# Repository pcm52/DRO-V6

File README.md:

# DRO-V6
Digital Readout sketch files for the Arduino IDE

Schematic and PCB layout files for both the DRO and Encoder boards in Eagle format.

See pcm52.com for more details on construction.

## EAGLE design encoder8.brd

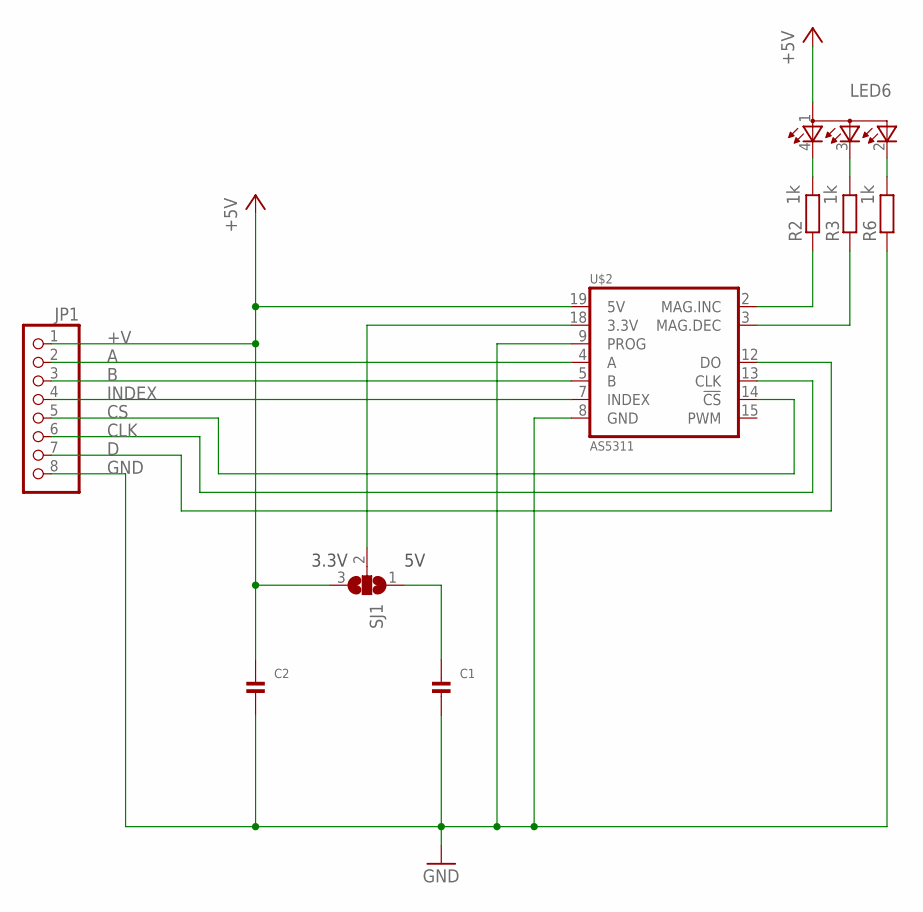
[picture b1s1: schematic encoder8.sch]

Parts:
C1, C2: CAP_CERAMIC0805; 0805
JP1: PINHD-1X8BIG; 1X08-BIG
LED6: RGB; RGB_LED_0805
R2, R3, R6: 1k; M0805
SJ1: SJ2W; SJ_2
U$2: AS5311; TSSOP.20

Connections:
+5V: LED6.1 (CA)
+V: C2.1, JP1.1, SJ1.3, U$2.19 (5V)
A: JP1.2, U$2.4 (A)
B: JP1.3, U$2.5 (B)
CLK: JP1.6, U$2.13 (CLK)
CS: JP1.5, U$2.14 (!CS)
D: JP1.7, U$2.12 (DO)
DEC: R3.1, U$2.3 (MAG.DEC)
GND: C1.2, C2.2, JP1.8, R6.1, U$2.8 (GND), U$2.9 (PROG)
INC: R2.1, U$2.2 (MAG.INC)
INDEX: JP1.4, U$2.7 (INDEX)
unnamed: C1.1, SJ1.1
unnamed: LED6.4 (CRED), R2.2
unnamed: LED6.3 (CGREEN), R3.2
unnamed: LED6.2 (CBLUE), R6.2
unnamed: SJ1.2, U$2.18 (3.3V)

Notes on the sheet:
3.3V

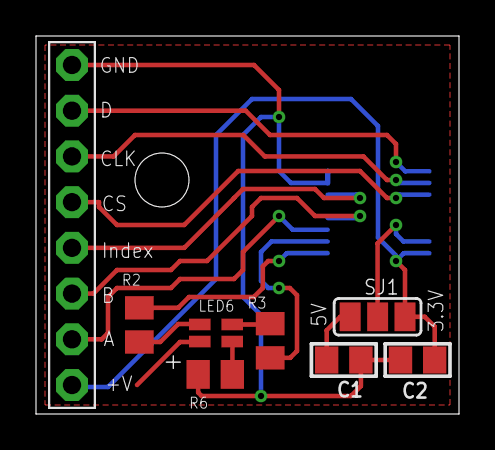
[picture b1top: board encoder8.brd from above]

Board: 2 copper layers, 23.5 x 21.0 mm, 9 parts (1 on the bottom side), 15 nets.

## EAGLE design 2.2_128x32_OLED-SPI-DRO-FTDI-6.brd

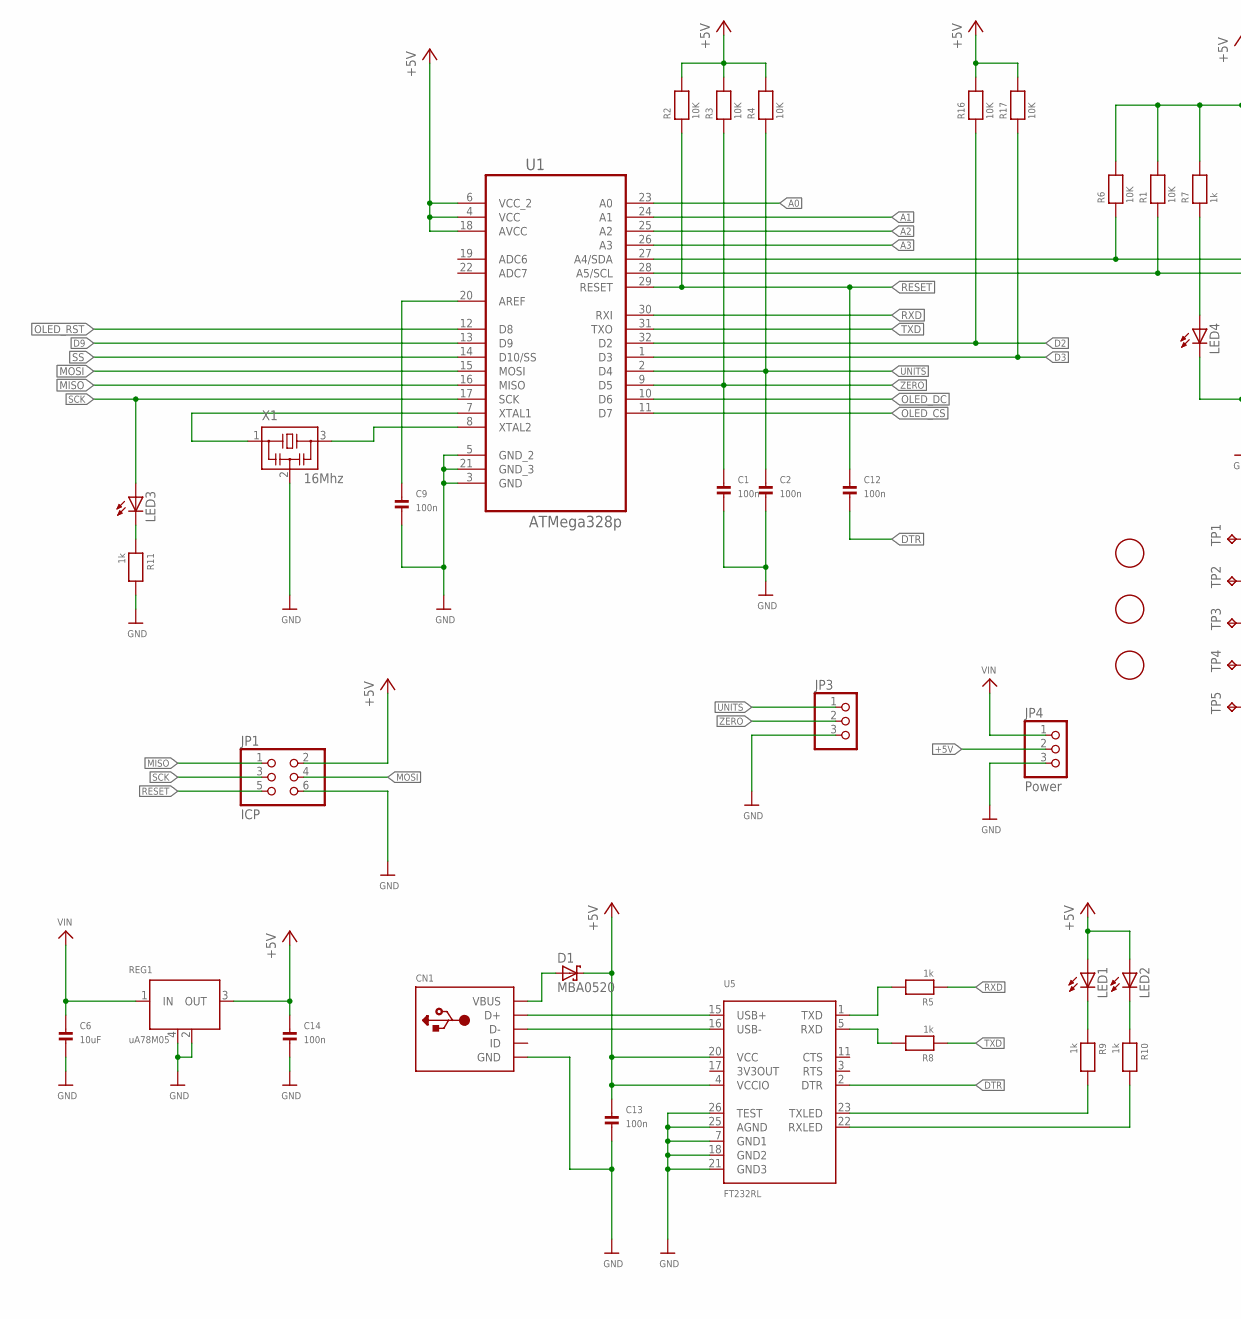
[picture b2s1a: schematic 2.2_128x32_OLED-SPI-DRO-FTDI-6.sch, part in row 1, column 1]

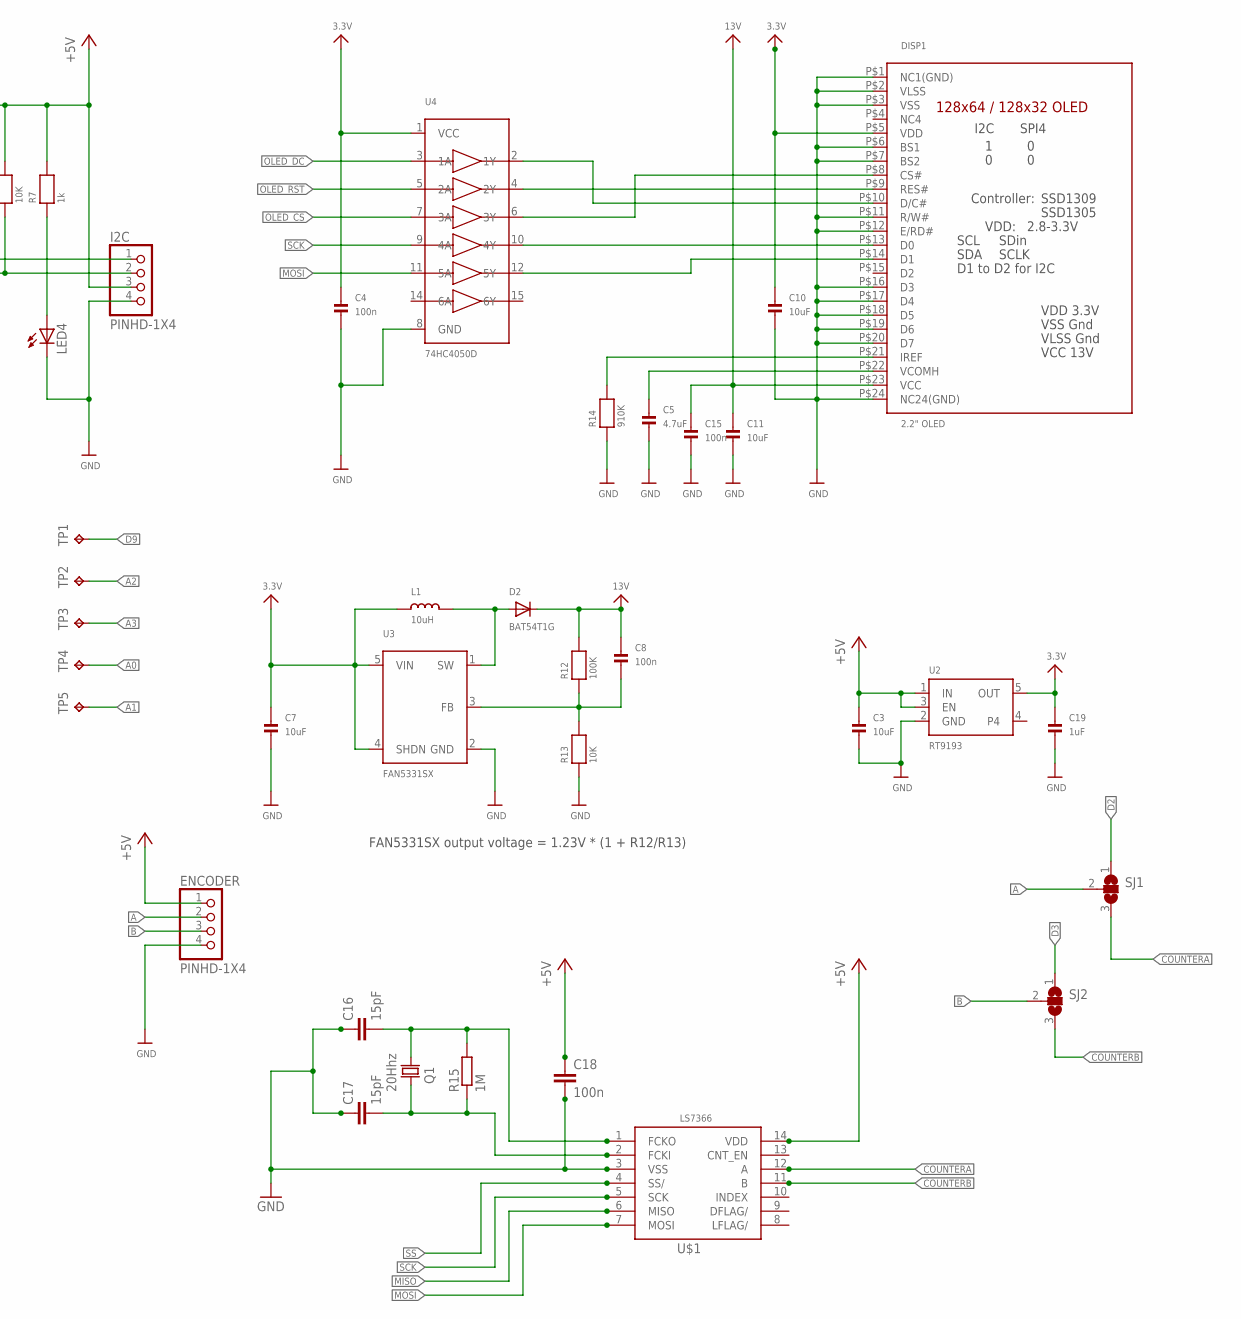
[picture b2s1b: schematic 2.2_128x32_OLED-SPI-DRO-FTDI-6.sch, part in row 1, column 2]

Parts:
C1, C2, C4, C8, C9, C12, C13, C14, C15: 100n; 0805
C3, C6, C7, C10, C11: 10uF; 0805
C5: 4.7uF; 0805
C16, C17: 15pF; C0805
C18: 100n; C0805
C19: 1uF; 0805
CN1: USBMINIB; USB-MINIB
D1: MBA0520; SOD123
D2: BAT54T1G; SOD-123
DISP1: 2.2" OLED; 1.5-128X64-TOP-CONTACT
ENCODER: PINHD-1X4; 1X04-BIG
I2C: PINHD-1X4; 1X04-BIG
JP1: ICP; 2X03
JP3: PINHD-1X3; 1X03
JP4: Power; 1X03
L1: 10uH; INDUCTOR_1007
LED1, LED2, LED3, LED4: LEDCHIPLED_0805; CHIPLED_0805
Q1: 20Hhz; F6-XTAL
R1, R2, R3, R4, R6, R13, R16, R17: 10K; 0805
R5, R7, R8, R9, R10, R11: 1k; 0805
R12: 100K; 0805
R14: 910K; 0805
R15: 1M; M0805
REG1: uA78M05; UA78M05
SJ1, SJ2: SJ2W; SJ_2
TP1, TP2, TP3, TP4, TP5: TPTP08R; TP08R
U1: ATMega328p; TQFP-32
U2: RT9193; SOT23-5
U3: FAN5331SX; SOT23-5
U4: 74HC4050D; SOIC16
U5: FT232RL; SSOP28DB
U$1: LS7366; SO14
U$2, U$6, U$28: FIDUCIAL; FIDUCIAL_1MM
X1: 16Mhz; CSTCE-CRYSTAL-OSC

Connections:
3.3V: C4.1, C7.1, C10.1, C19.1, DISP1.P$5 (VDD), L1.P$1 (1), U2.5 (OUT), U3.4 (SHDN), U3.5 (VIN), U4.1 (VCC)
3V3OUT: U5.17 (3V3OUT)
13V: C8.1, C11.1, C15.1, D2.C, DISP1.P$23 (VCC), R12.2
+5V: C3.1, C13.1, C14.1, C18.1, D1.C, ENCODER.1, I2C.3, JP1.2, JP4.2, LED1.A, LED2.A, R1.2, R2.2, R3.2, R4.2, R6.2, R7.2, R16.2, R17.2, REG1.3 (OUT), U1.4 (VCC), U1.6 (VCC_2), U1.18 (AVCC), U2.1 (IN), U2.3 (EN), U5.4 (VCCIO), U5.20 (VCC), U$1.14 (VDD)
A: ENCODER.2, SJ1.2
A0: TP4.TP, U1.23 (A0)
A1: TP5.TP, U1.24 (A1)
A2: TP2.TP, U1.25 (A2)
A3: TP3.TP, U1.26 (A3)
B: ENCODER.3, SJ2.2
COUNTERA: SJ1.3, U$1.12 (A)
COUNTERB: SJ2.3, U$1.11 (B)
CS: DISP1.P$8 (CS#), U4.6 (3Y)
D0: DISP1.P$13 (D0), U4.10 (4Y)
D1: DISP1.P$14 (D1), U4.12 (5Y)
D2: R16.1, SJ1.1, U1.32 (D2)
D3: R17.1, SJ2.1, U1.1 (D3)
D9: TP1.TP, U1.13 (D9)
DC: DISP1.P$10 (D/C#), U4.2 (1Y)
DTR: C12.2, U5.2 (DTR)
GND: C1.2, C2.2, C3.2, C4.2, C5.2, C6.2, C7.2, C9.2, C10.2, C11.2, C13.2, C14.2, C15.2, C16.1, C17.1, C18.2, C19.2, CN1.GND, DISP1.P$1 (NC1(GND)), DISP1.P$2 (VLSS), DISP1.P$3 (VSS), DISP1.P$6 (BS1), DISP1.P$7 (BS2), DISP1.P$11 (R/W#), DISP1.P$12 (E/RD#), DISP1.P$16 (D3), DISP1.P$17 (D4), DISP1.P$18 (D5), DISP1.P$19 (D6), DISP1.P$20 (D7), DISP1.P$24 (NC24(GND)), ENCODER.4, I2C.4, JP1.6, JP3.3, JP4.3, LED4.C, R11.2, R13.1, R14.1, REG1.2 (COMMON1), REG1.4 (COMMON2), U1.3 (GND), U1.5 (GND_2), U1.21 (GND_3), U2.2 (GND), U3.2 (GND), U4.8 (GND), U5.7 (GND1), U5.18 (GND2), U5.21 (GND3), U5.25 (AGND), U5.26 (TEST), U$1.3 (VSS), X1.2
MISO: JP1.1, U1.16 (MISO), U$1.6 (MISO)
MOSI: JP1.4, U1.15 (MOSI), U4.11 (5A), U$1.7 (MOSI)
unnamed: D2.A, L1.P$2 (2), U3.1 (SW)
unnamed: U1.7 (XTAL1), X1.1
unnamed: DISP1.P$21 (IREF), R14.2
unnamed: C8.2, R12.1, R13.2, U3.3 (FB)
unnamed: C5.1, DISP1.P$22 (VCOMH)
unnamed: U1.8 (XTAL2), X1.3
unnamed: C9.1, U1.20 (AREF)
unnamed: CN1.D+, U5.15 (USB+)
unnamed: CN1.D-, U5.16 (USB-)
unnamed: CN1.VBUS, D1.A
unnamed: R5.2, U5.1 (TXD)
unnamed: R8.2, U5.5 (RXD)
unnamed: R9.2, U5.23 (TXLED)
unnamed: R10.2, U5.22 (RXLED)
unnamed: LED3.C, R11.1
unnamed: LED1.C, R9.1
unnamed: LED2.C, R10.1
unnamed: LED4.A, R7.1
unnamed: C16.2, Q1.P$2 (2), R15.2, U$1.1 (FCKO)
unnamed: C17.2, Q1.P$1 (1), R15.1, U$1.2 (FCKI)
OLED_CS: U1.11 (D7), U4.7 (3A)
OLED_DC: U1.10 (D6), U4.3 (1A)
OLED_RST: U1.12 (D8), U4.5 (2A)
RES: DISP1.P$9 (RES#), U4.4 (2Y)
RESET: C12.1, JP1.5, R2.1, U1.29 (RESET)
RXD: R5.1, U1.30 (RXI)
SCK: JP1.3, LED3.A, U1.17 (SCK), U4.9 (4A), U$1.5 (SCK)
SCL: I2C.2, R1.1, U1.28 (A5/SCL)
SDA: I2C.1, R6.1, U1.27 (A4/SDA)
SS: U1.14 (D10/SS), U$1.4 (SS/)
TXD: R8.1, U1.31 (TXO)
UNITS: C2.1, JP3.1, R4.1, U1.2 (D4)
VIN: C6.1, JP4.1, REG1.1 (IN)
ZERO: C1.1, JP3.2, R3.1, U1.9 (D5)

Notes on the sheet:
FAN5331SX output voltage = 1.23V * (1 + R12/R13)

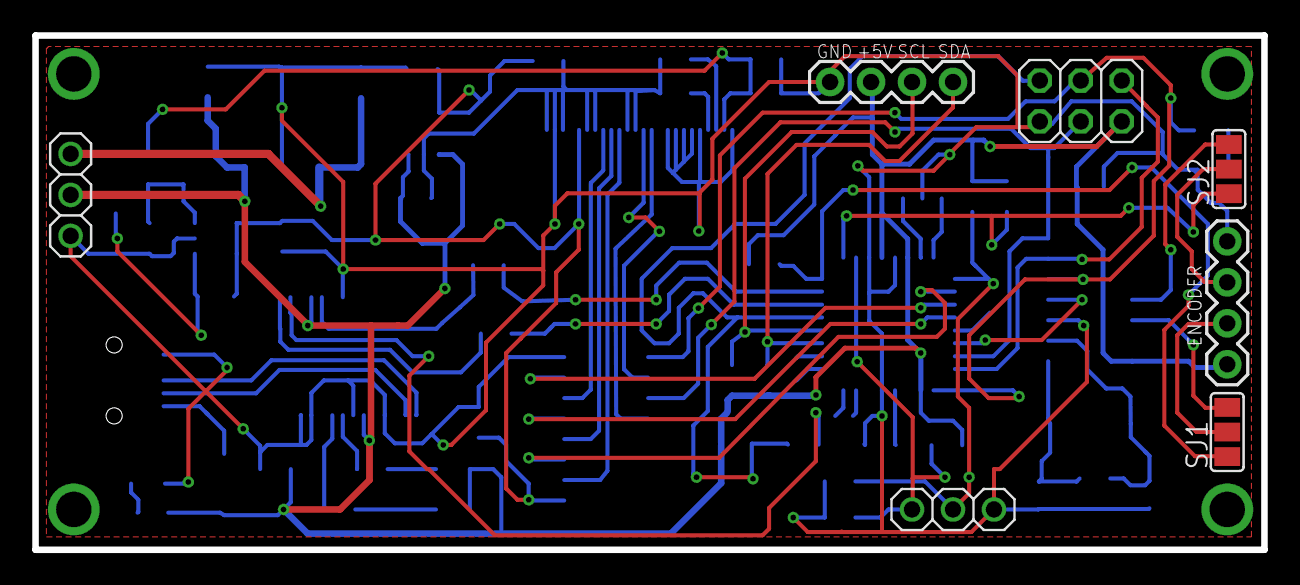
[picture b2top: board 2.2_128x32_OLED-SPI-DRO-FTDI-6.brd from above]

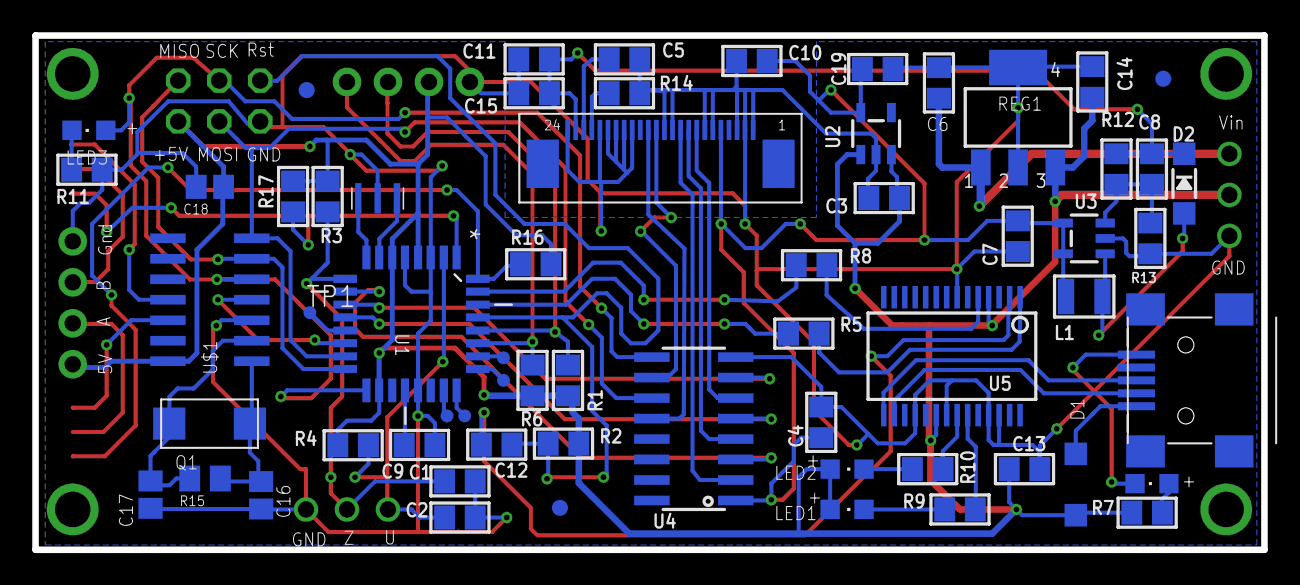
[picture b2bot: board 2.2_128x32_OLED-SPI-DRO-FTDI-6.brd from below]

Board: 2 copper layers, 76.2 x 31.9 mm, 69 parts (62 on the bottom side), 56 nets.

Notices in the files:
parts and their libraries:
microbuilder: This work is placed in the public domain, and may be freely used for commercial and non-commercial work with the following conditions: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
